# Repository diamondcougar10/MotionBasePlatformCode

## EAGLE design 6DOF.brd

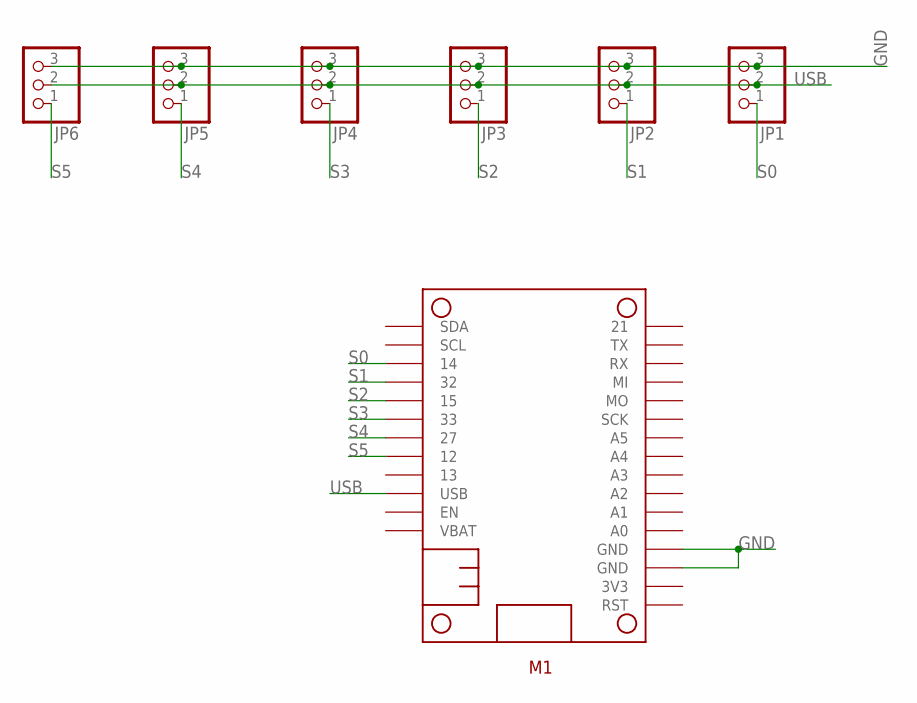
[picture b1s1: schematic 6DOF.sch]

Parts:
JP1, JP2, JP3, JP4, JP5, JP6: PINHD-1X3; 1X03
M1: RARNDT-MISCELANEOUS_FEATHERBOARD_ESP32FETHERWING_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; RARNDT-MISCELANEOUS_FEATHERBOARD_ESP32

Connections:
GND: JP1.3, JP2.3, JP3.3, JP4.3, JP5.3, JP6.3, M1.3 (GND), M1.4 (GND)
S0: JP1.1, M1.19 (14)
S1: JP2.1, M1.20 (32)
S2: JP3.1, M1.21 (15)
S3: JP4.1, M1.22 (33)
S4: JP5.1, M1.23 (27)
S5: JP6.1, M1.24 (12)
USB: JP1.2, JP2.2, JP3.2, JP4.2, JP5.2, JP6.2, M1.26 (USB)

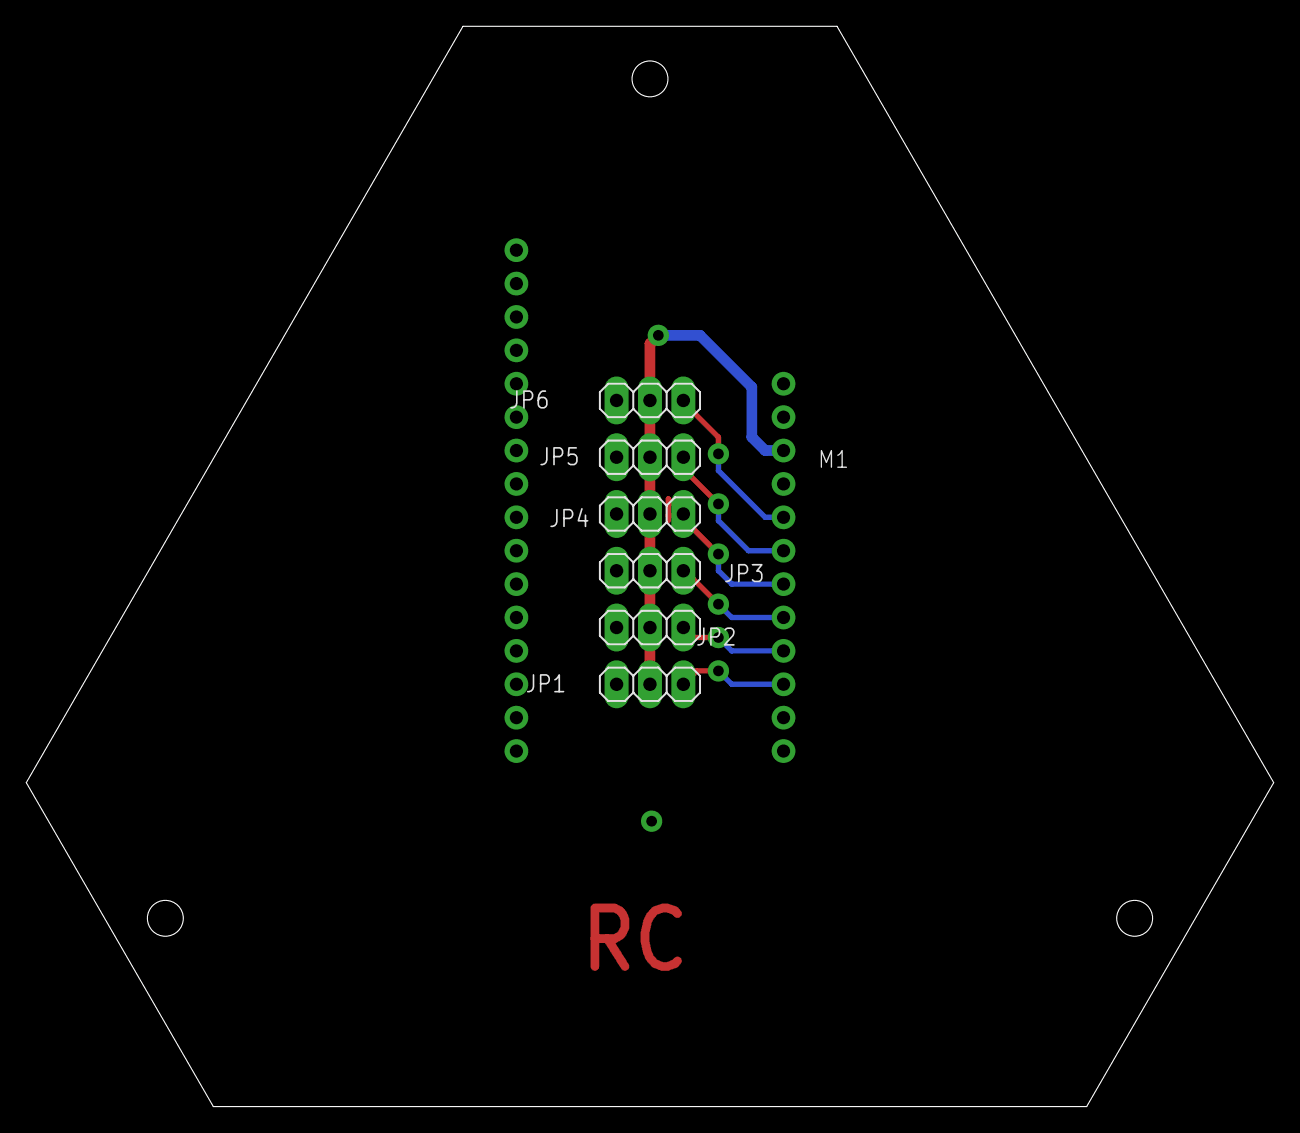
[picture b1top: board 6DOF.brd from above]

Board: 2 copper layers, 94.9 x 82.2 mm, 7 parts (0 on the bottom side), 8 nets.
